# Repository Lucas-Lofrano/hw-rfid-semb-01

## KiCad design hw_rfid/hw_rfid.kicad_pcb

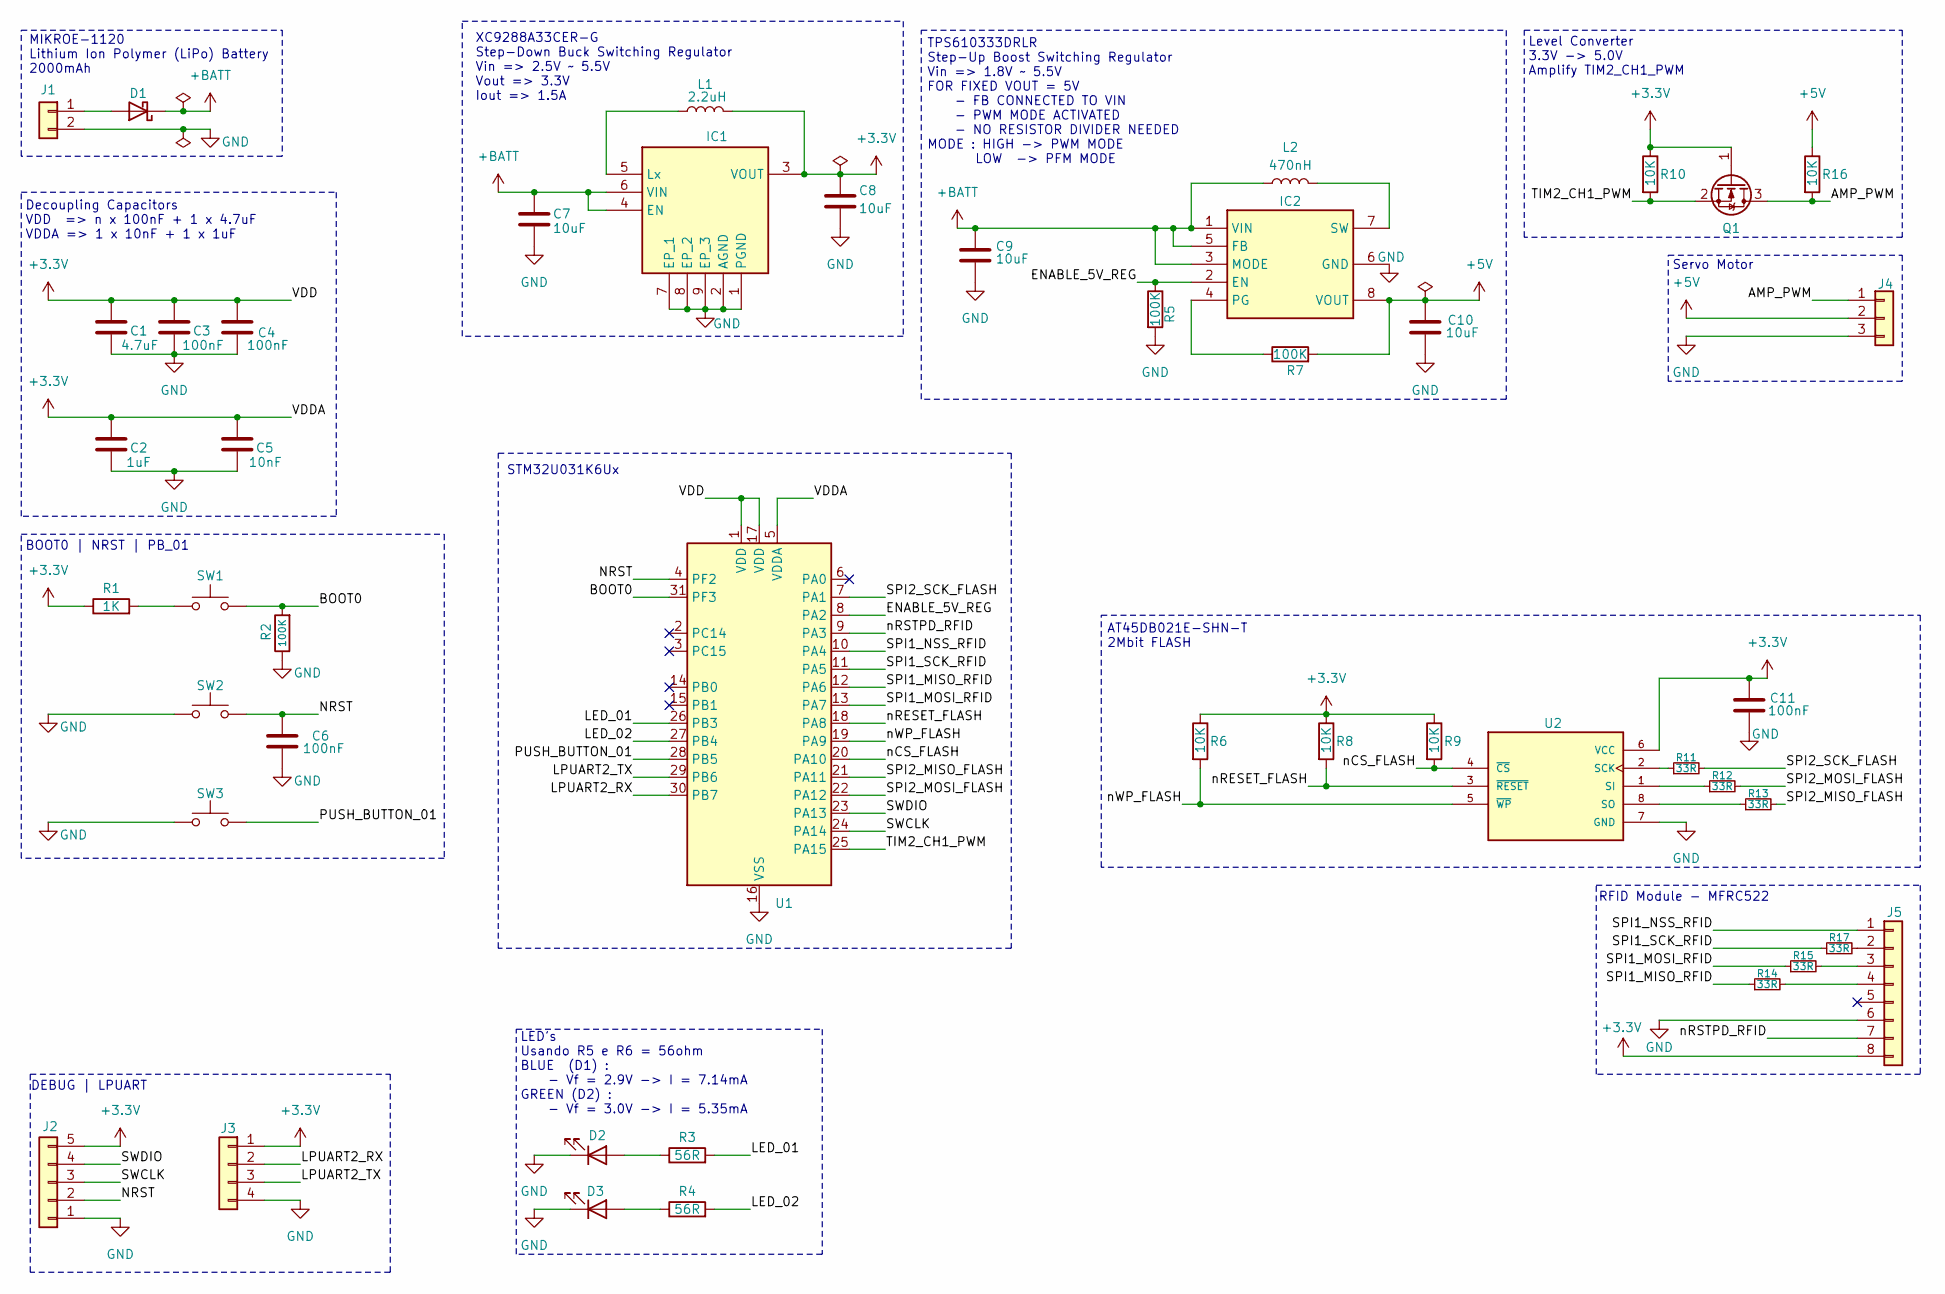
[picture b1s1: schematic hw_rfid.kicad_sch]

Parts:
C1: 4.7uF; C_0603_1608Metric; Mouser Part Number 963-TMK107BBJ475KA-T
C2: 1uF; C_0603_1608Metric; Mouser Part Number 963-MLAST168SB7105MT
C3, C4, C6, C11: 100nF; C_0603_1608Metric; Mouser Part Number 963-MSASG063SB5104KF
C5: 10nF; C_0603_1608Metric; Mouser Part Number 963-MLASU063SB5103KF
C7, C8, C9, C10: 10uF; C_0805_2012Metric; Mouser Part Number 187-CL21A106KAYNNNG
D1: SS26; D_SMA; Mouser Part Number 78-SS2FN6-M3/H
D2: BLUE; LED_0805_2012Metric; Mouser Part Number 755-SMLMN2BCTT86C
D3: GREEN; LED_0805_2012Metric; Mouser Part Number 755-SMLMN2ECTT86C
IC1: XC9288A33CER-G; USP-6C; Mouser Part Number 865-XC9288A33CER-G
IC2: TPS610333DRLR; SOTFL50P160X60-8N; Mouser Part Number 595-TPS610333DRLR
J1: Conn_01x02; JST_XH_S2B-XH-A-1_1x02_P2.50mm_Horizontal; Mouser Part Number 306-S2B-XH-ALFSN
J2: Conn_01x05; PinHeader_1x05_P2.54mm_Vertical; Mouser Part Number 649-1012937890502BLF
J3: Conn_01x04; PinHeader_1x04_P2.54mm_Vertical; Mouser Part Number 200-TSW10407TS
J4: Conn_01x03; PinHeader_1x03_P2.54mm_Vertical; Mouser Part Number 200-HTSW10307TS
J5: Conn_01x08; PinHeader_1x08_P2.54mm_Vertical; Mouser Part Number 200-MTSW10807TS185
L1: 2.2uH; L_0805_2012Metric; Mouser Part Number 530-F1C1-201612-2R2M
L2: 470nH; L_0805_2012Metric; Mouser Part Number 530-F1C1-201612-R47M
Q1: 2N7002; SOT-23; Mouser Part Number 512-2N7002
R1: 1K; R_0805_2012Metric; Mouser Part Number 303-0805W8J0102T5E
R2, R5, R7: 100K; R_0805_2012Metric; Mouser Part Number 303-0805W8F1003T5E
R3, R4: 56R; R_0805_2012Metric; Mouser Part Number 303-0805W8J0560T5E
R6, R8, R9, R10, R16: 10K; R_0805_2012Metric; Mouser Part Number 303-0805W8J0103T5E
R11, R12, R13, R14, R15, R17: 33R; R_0603_1608Metric; Mouser Part Number 667-ERJ-PA3D33R0V
SW1, SW2, SW3: SW_Push; SW_DIP_SPSTx01_Slide_6.7x4.1mm_W6.73mm_P2.54mm_LowProfile_J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; Mouser Part Number 653-A6SN-1101
U1: STM32U031K6Ux; QFN-32-1EP_5x5mm_P0.5mm_EP3.45x3.45mm; Mouser Part Number 511-STM32U031K6U6
U2: AT45DB021E-SHN-T; SOIC127P798X216-8N; PARTREV 8789I; Mouser Part Number 556-AT45DB021E-SHN-T

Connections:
+3.3V: C1.1, C2.1, C3.1, C4.1, C5.1, C8.1, C11.1, IC1.3 (VOUT), J2.5, J3.1, J5.8, L1.2, Q1.1 (G), R1.1, R6.1, R8.1, R9.1, R10.1, U1.1 (VDD), U1.5 (VDDA), U1.17 (VDD), U2.6 (VCC)
+5V: C10.1, IC2.8 (VOUT), J4.2, R7.2, R16.1
+BATT: C7.1, C9.1, D1.1 (K), IC1.4 (EN), IC1.6 (VIN), IC2.1 (VIN), IC2.3 (MODE), IC2.5 (FB), L2.1
/AMP_PWM: J4.1, Q1.3 (D), R16.2
/BOOT0: R2.2, SW1.2, U1.31 (PF3)
/ENABLE_5V_REG: IC2.2 (EN), R5.1, U1.8 (PA2)
/LED_01: R3.2, U1.26 (PB3)
/LED_02: R4.2, U1.27 (PB4)
/LPUART2_RX: J3.2, U1.30 (PB7)
/LPUART2_TX: J3.3, U1.29 (PB6)
/NRST: C6.1, J2.2, SW2.2, U1.4 (PF2)
/PUSH_BUTTON_01: SW3.2, U1.28 (PB5)
/SPI1_MISO_RFID: R14.1, U1.12 (PA6)
/SPI1_MOSI_RFID: R15.1, U1.13 (PA7)
/SPI1_NSS_RFID: J5.1, U1.10 (PA4)
/SPI1_SCK_RFID: R17.1, U1.11 (PA5)
/SPI2_MISO_FLASH: R13.2, U1.21 (PA11)
/SPI2_MOSI_FLASH: R12.2, U1.22 (PA12)
/SPI2_SCK_FLASH: R11.2, U1.7 (PA1)
/SWCLK: J2.3, U1.24 (PA14)
/SWDIO: J2.4, U1.23 (PA13)
/TIM2_CH1_PWM: Q1.2 (S), R10.2, U1.25 (PA15)
/nCS_FLASH: R9.2, U1.20 (PA10), U2.4 (~CS)
/nRESET_FLASH: R8.2, U1.18 (PA8), U2.3 (~RESET)
/nRSTPD_RFID: J5.7, U1.9 (PA3)
/nWP_FLASH: R6.2, U1.19 (PA9), U2.5 (~WP)
GND: C1.2, C2.2, C3.2, C4.2, C5.2, C6.2, C7.2, C8.2, C9.2, C10.2, C11.2, D2.1 (K), D3.1 (K), IC1.1 (PGND), IC1.2 (AGND), IC1.7 (EP_1), IC1.8 (EP_2), IC1.9 (EP_3), IC2.6 (GND), J1.2, J2.1, J3.4, J4.3, J5.6, R2.1, R5.2, SW2.1, SW3.1, U1.16 (VSS), U1.32 (VSS), U1.33 (VSS), U2.7 (GND)
unnamed: D1.2 (A), J1.1
unnamed: D2.2 (A), R3.1
unnamed: D3.2 (A), R4.1
unnamed: IC1.5 (Lx), L1.1
unnamed: IC2.4 (PG), R7.1
unnamed: IC2.7 (SW), L2.2
unnamed: J5.2, R17.2
unnamed: J5.3, R15.2
unnamed: J5.4, R14.2
unnamed: R1.2, SW1.1
unnamed: R11.1, U2.2 (SCK)
unnamed: R12.1, U2.1 (SI)
unnamed: R13.1, U2.8 (SO)

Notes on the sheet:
XC9288A33CER-G Step-Down Buck Switching Regulator Vin => 2.5V ~ 5.5V Vout => 3.3V Iout => 1.5A
TPS610333DRLR Step-Up Boost Switching Regulator Vin => 1.8V ~ 5.5V FOR FIXED VOUT = 5V - FB CONNECTED TO VIN - PWM MODE ACTIVATED - NO RESISTOR DIVIDER NEEDED MODE : HIGH -> PWM MODE LOW -> PFM MODE
STM32U031K6Ux
Decoupling Capacitors VDD => n x 100nF + 1 x 4.7uF VDDA => 1 x 10nF + 1 x 1uF
AT45DB021E-SHN-T 2Mbit FLASH
BOOT0 | NRST | PB_01
LED's Usando R5 e R6 = 56ohm BLUE (D1) : - Vf = 2.9V -> I = 7.14mA GREEN (D2) : - Vf = 3.0V -> I = 5.35mA
Level Converter 3.3V -> 5.0V Amplify TIM2_CH1_PWM
DEBUG | LPUART
Servo Motor
MIKROE-1120 Lithium Ion Polymer (LiPo) Battery 2000mAh
RFID Module - MFRC522

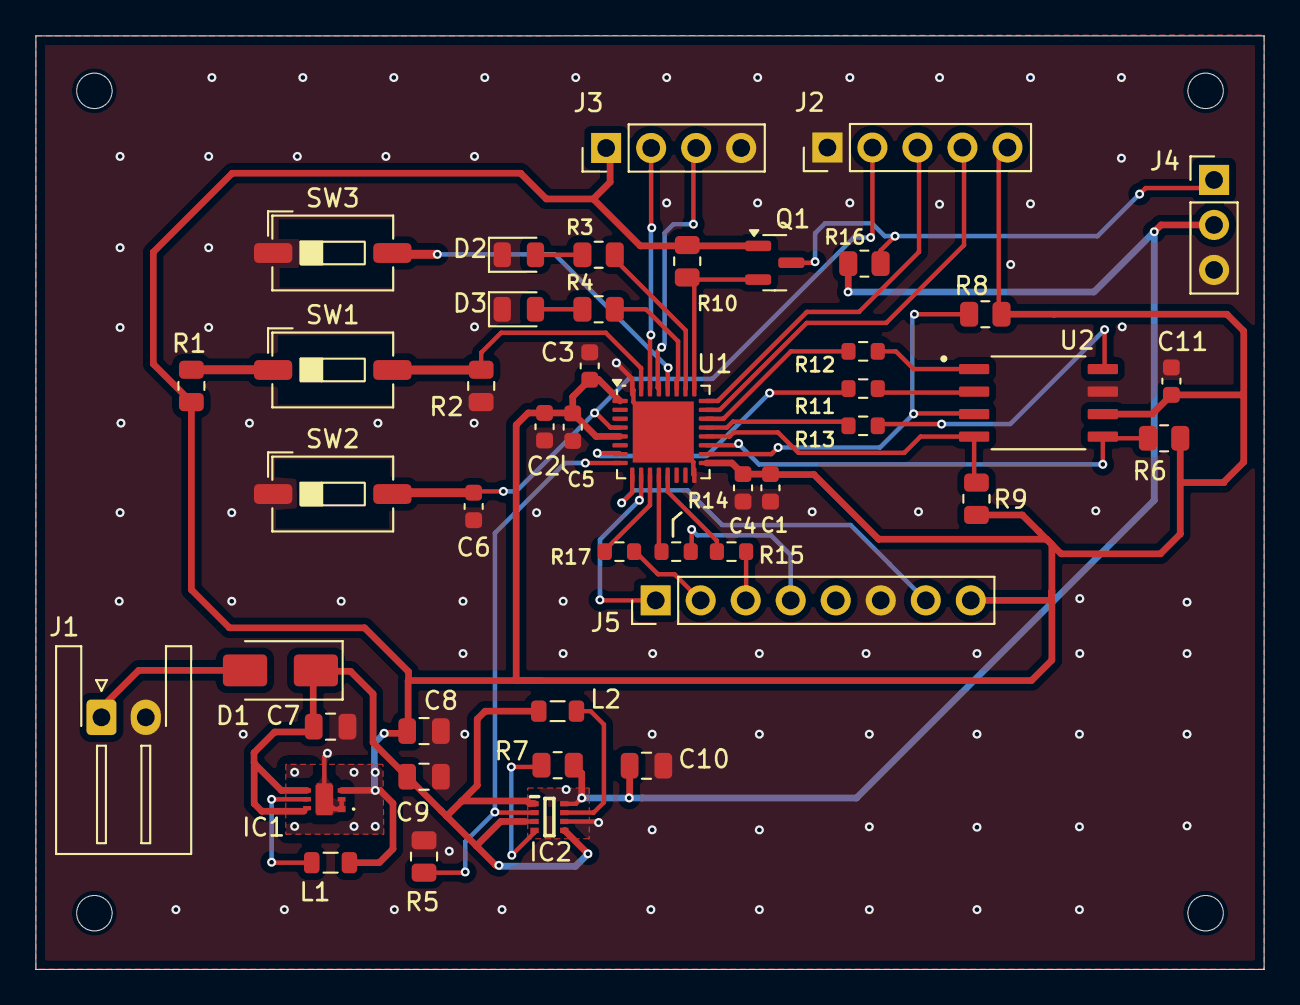
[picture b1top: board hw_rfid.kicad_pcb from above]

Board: 2 copper layers, 69.3 x 52.7 mm, 46 parts (0 on the bottom side), 40 nets.

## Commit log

2025-04-01 Initial commit HW-RFID
2025-04-06 feat: Changing the way of import the libs
2025-04-26 PLACA atualizada
2025-04-26 Placa finalizada para análise
2025-04-28 modificações placa
2025-04-29 vista pelo marcelo mas nao reorganizada
2025-05-01 Finalmente finalizada para sempre
2025-05-01 Final pt2 o inimigo agora é outro
